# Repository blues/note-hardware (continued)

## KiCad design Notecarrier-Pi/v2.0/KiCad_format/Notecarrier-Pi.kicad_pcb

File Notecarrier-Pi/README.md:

# Notecarrier PI
Daughter board to integrate Notecard with Raspberry PI compatible hardware interface.
  - Schematics
  - Bills of material
  - PCB layouts and Gerber files
  - Dimensioned drawings
  - 3D models
  - KiCad design files ([v1.1/KiCad_format](v1.1/KiCad_format) and [v2.0/KiCad_format](v2.0/KiCad_format); v2.0 was authored in OrCAD/Allegro, for which no KiCad importer exists, so its port was built as a validated delta from the v1.1 port — see its [Porting-Notes](v2.0/KiCad_format/documentation/Porting-Notes.md))

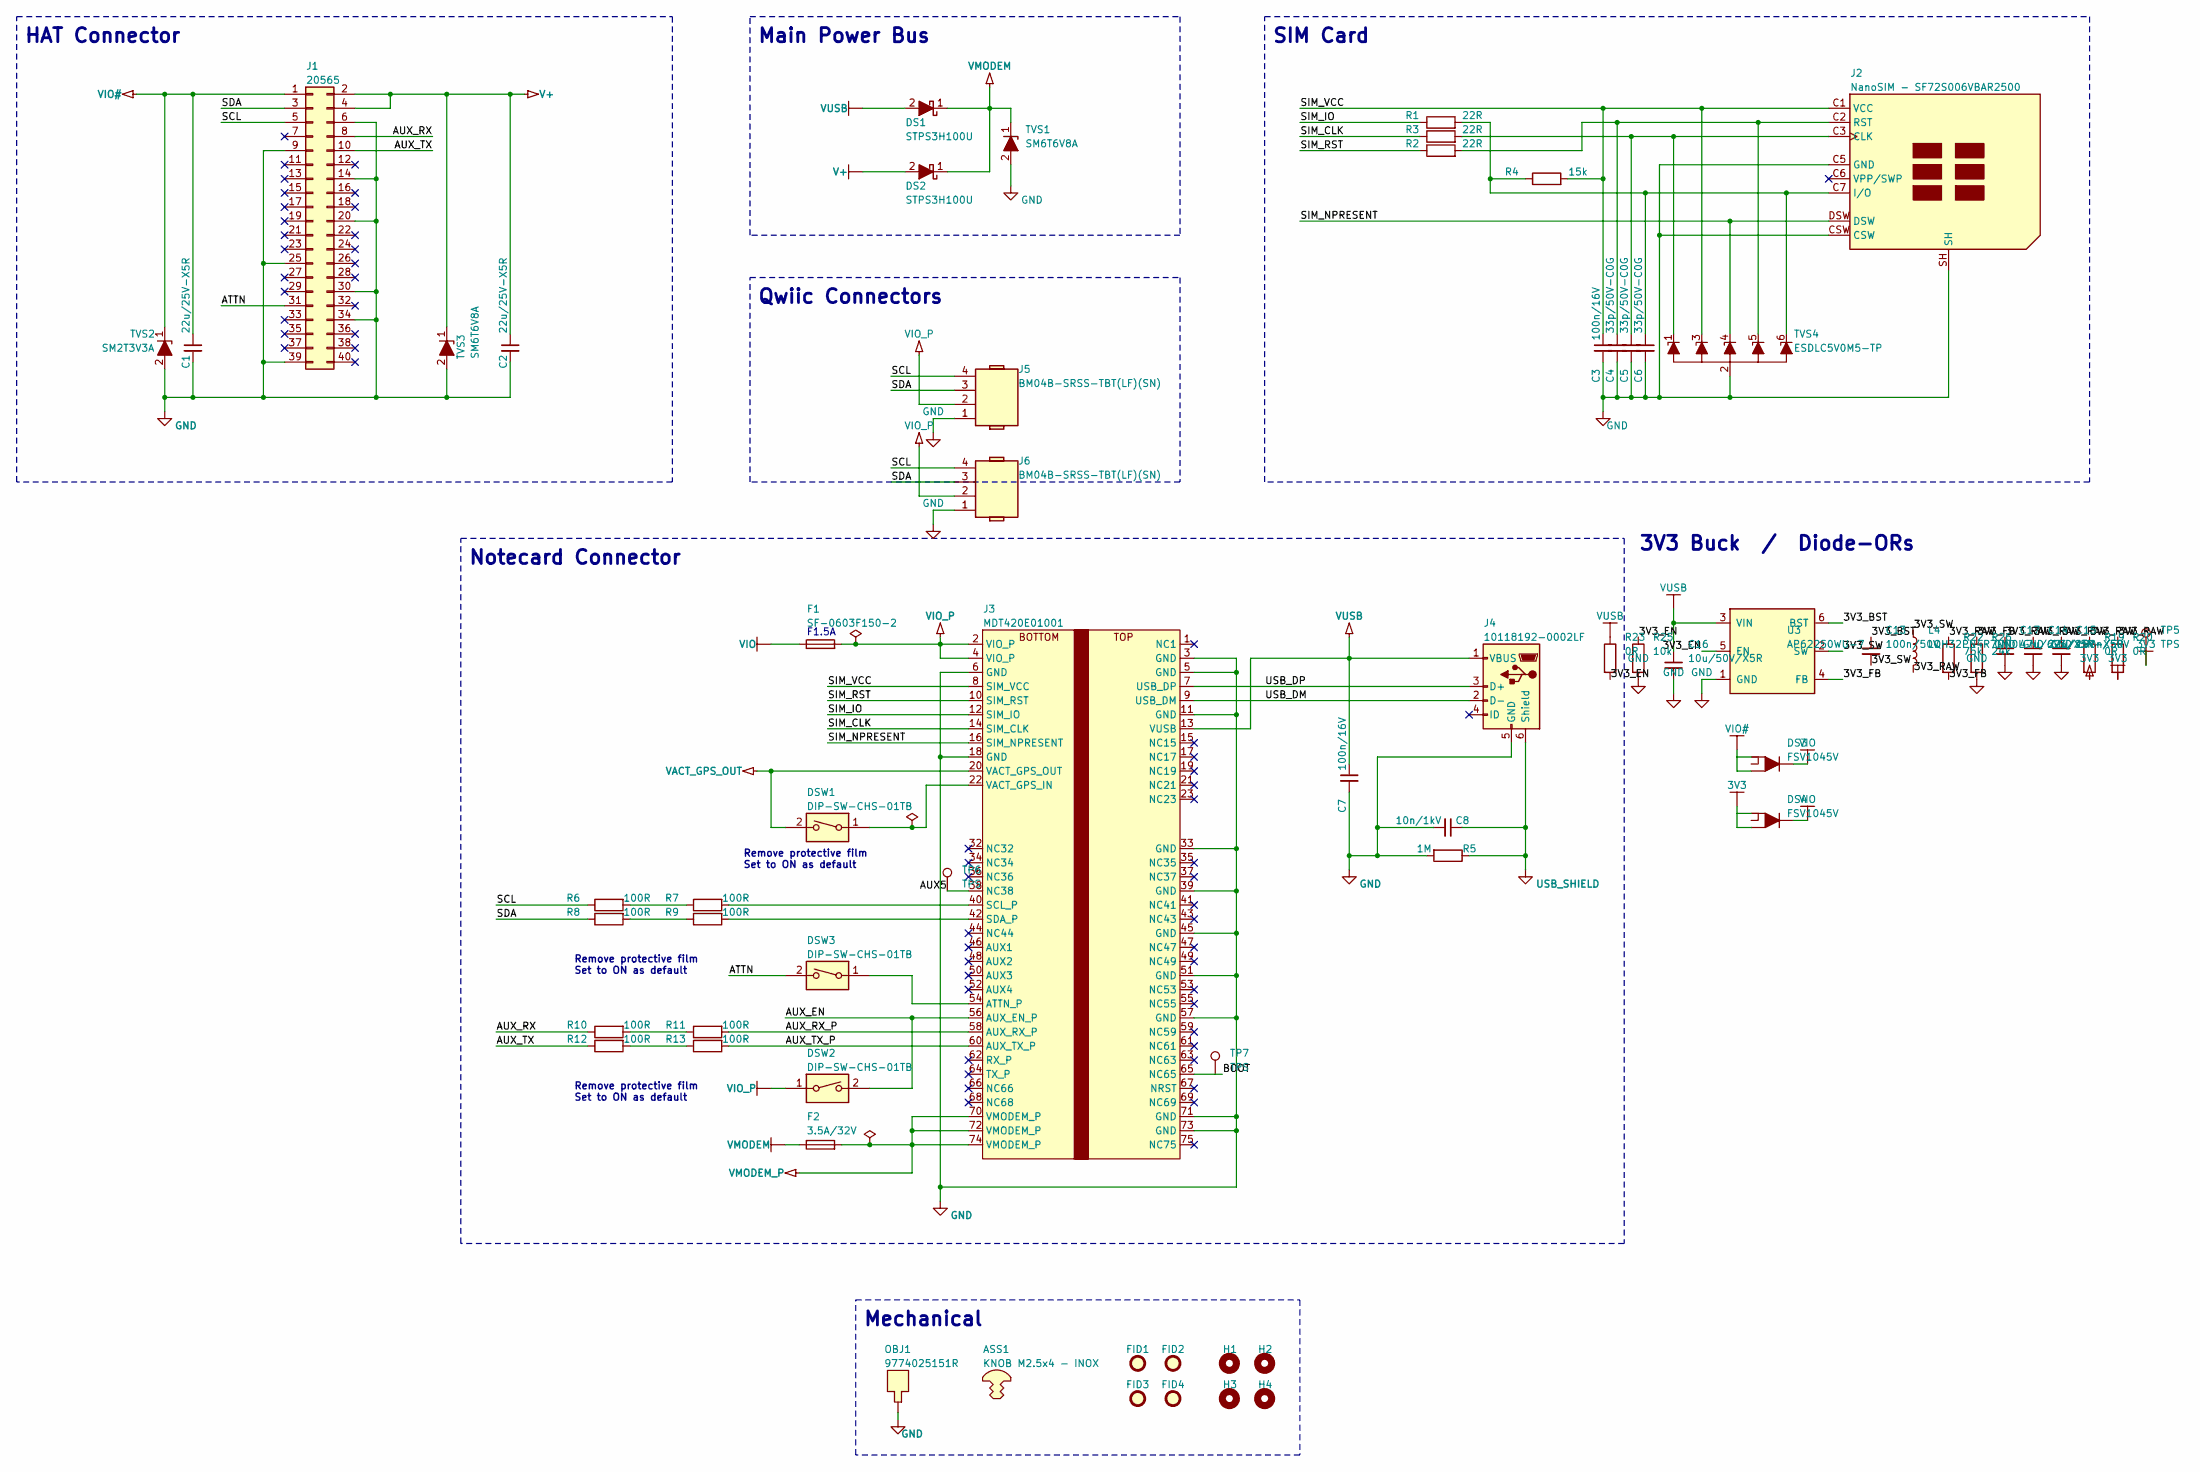
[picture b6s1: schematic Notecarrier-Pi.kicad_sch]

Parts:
ASS1: KNOB M2.5x4 - INOX; MPN 179-5691
C1, C2, C14: 22u/25V-X5R; CS-C-1206
C3, C7: 100n/16V; CS-C-0402
C4, C5, C6: 33p/50V-C0G; CS-C-0402
C8: 10n/1kV; CS-C-1206
C13, C15: 100n/50V; CS-C-0603
C16: 10u/50V/X5R; CS-C-1206
C17: 47u/6V3/X5R; CS-C-0603
DS1, DS2: STPS3H100U; SMB; MPN STPS3H100U
DS3, DS4: FSV1045V; TO277-3; MPN FSV1045V
DSW1, DSW2, DSW3: DIP-SW-CHS-01TB; DSS-CHS-01TB
F1: SF-0603F150-2; FS-0603; MPN SF-0603F150-2
F2: 3.5A/32V; FS-0603; MPN 0603SFV350F/32-2
FID1, FID2, FID3, FID4: TPS; FIDUCIAL
H1, H2, H3, H4: MountingHole; FORO-0270-U_smaller-clearance
J1: 20565; J-20x2-0254-FDT-SSQX03; MPN 20565
J2: NanoSIM - SF72S006VBAR2500; J-NANOSIM-SF72S006VBA_NO-FILL; MPN SF72S006VBAR2500
J3: MDT420E01001; J-75-0050-MOS-M2-E
J4: 10118192-0002LF; J-5-0065-FOS-USB10118192-NOF; MPN 10118192-0002LF
J5, J6: BM04B-SRSS-TBT(LF)(SN); J-4-0100-MDS-SH; MPN BM04B-SRSS-TBT(LF)(SN)
L4: LQH32PN4R7NN0L; LS-LQH32PN; MPN LQH32PN4R7NN0L
OBJ1: 9774025151R; DIST-WASMSIM0250
R1, R2, R3: 22R; RS-0603
R4: 15k; RS-0402
R5: 1M; RS-1206
R6, R7, R8, R9, R10, R11, R12, R13: 100R; RS-0402
R19, R20: 0R; RS-0603
R22: 75k; RS-0402
R23: 0R; RS-0402
R25: 10k; RS-0402
R26: 24k; RS-0402
TP5: TPS; TPS-0100
TP6, TP7: TPS; TPS-0150
TVS1, TVS3: SM6T6V8A; SMB
TVS2: SM2T3V3A; D-DO216AA_NO-SILK
TVS4: ESDLC5V0M5-TP; SOT666_NO-SILK
U3: AP62250WU-7; SOT23-6-DBV; MPN AP62250WU-7

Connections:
3V3: DS4.1 (A), DS4.2 (A), R19.2, R20.2, TP5.1
/3V3_BST: C13.1, U3.6 (BST)
/3V3_EN: R23.2, R25.1, U3.5 (EN)
/3V3_FB: R22.2, R26.1, U3.4 (FB)
/3V3_RAW: C14.1, C15.1, C17.1, L4.2, R19.1, R20.1, R22.1
/3V3_SW: C13.2, L4.1, U3.2 (SW)
/ATTN: DSW3.2, J1.31
/AUX5: J3.38 (NC38), TP6.1
/AUX_EN: DSW2.2, J3.56 (AUX_EN_P)
/AUX_RX: J1.8, R10.1
/AUX_RX_P: J3.58 (AUX_RX_P), R11.2
/AUX_TX: J1.10, R12.1
/AUX_TX_P: J3.60 (AUX_TX_P), R13.2
/BOOT: J3.65 (NC65), TP7.1
/SCL: J1.5, J5.4, J6.4, R6.1
/SDA: J1.3, J5.3, J6.3, R8.1
/SIM_CLK: J3.14 (SIM_CLK), R3.1
/SIM_IO: J3.12 (SIM_IO), R1.1
/SIM_NPRESENT: J2.DSW, J3.16 (SIM_NPRESENT), TVS4.4 (K3)
/SIM_RST: J3.10 (SIM_RST), R2.1
/SIM_VCC: C3.1, J2.C1 (VCC), J3.8 (SIM_VCC), R4.2, TVS4.3 (K2)
/USB_DM: J3.9 (USB_DM), J4.2 (D-)
/USB_DP: J3.7 (USB_DP), J4.3 (D+)
GND: C1.2, C2.2, C3.2, C4.2, C5.2, C6.2, C7.2, C8.2, C14.2, C15.2, C16.2, C17.2, J1.6, J1.9, J1.14, J1.20, J1.25, J1.30, J1.34, J1.39, J2.C5 (GND), J2.CSW, J2.SH, J3.3 (GND), J3.5 (GND), J3.6 (GND), J3.11 (GND), J3.18 (GND), J3.33 (GND), J3.39 (GND), J3.45 (GND), J3.51 (GND), J3.57 (GND), J3.71 (GND), J3.73 (GND), J4.5 (GND), J5.1, J6.1, OBJ1.1, R5.2, R25.2, R26.2, TVS1.2 (A2), TVS2.2 (A2), TVS3.2 (A2), TVS4.2 (A), U3.1 (GND)
unnamed: C5.1, J2.C3 (CLK), R3.2, TVS4.1 (K1)
unnamed: C6.1, J2.C7 (I/O), R1.2, R4.1, TVS4.6 (K5)
unnamed: C4.1, J2.C2 (RST), R2.2, TVS4.5 (K4)
unnamed: DSW3.1, J3.54 (ATTN_P)
unnamed: J3.40 (SCL_P), R7.2
unnamed: J3.42 (SDA_P), R9.2
unnamed: DSW1.1, J3.22 (VACT_GPS_IN)
unnamed: C8.1, J4.6 (Shield), R5.1
unnamed: R6.2, R7.1
unnamed: R8.2, R9.1
unnamed: R10.2, R11.1
unnamed: R12.2, R13.1
V+: C2.1, DS2.2 (A), J1.2, J1.4, TVS3.1 (A1)
VACT_GPS_OUT: DSW1.2, J3.20 (VACT_GPS_OUT)
VIO: DS3.3 (K), DS4.3 (K), F1.1
VIO#: C1.1, DS3.1 (A), DS3.2 (A), J1.1, TVS2.1 (A1)
VIO_P: DSW2.1, F1.2, J3.2 (VIO_P), J3.4 (VIO_P), J5.2, J6.2
VMODEM: DS1.1 (K), DS2.1 (K), F2.1, TVS1.1 (A1)
VMODEM_P: F2.2, J3.70 (VMODEM_P), J3.72 (VMODEM_P), J3.74 (VMODEM_P)
VUSB: C7.1, C16.1, DS1.2 (A), J3.13 (VUSB), J4.1 (VBUS), R23.1, U3.3 (VIN)

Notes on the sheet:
Main Power Bus
Remove protective film Set to ON as default
Mechanical
Qwiic Connectors
HAT Connector
F1.5A
Notecard Connector
SIM Card
3V3 Buck / Diode-ORs

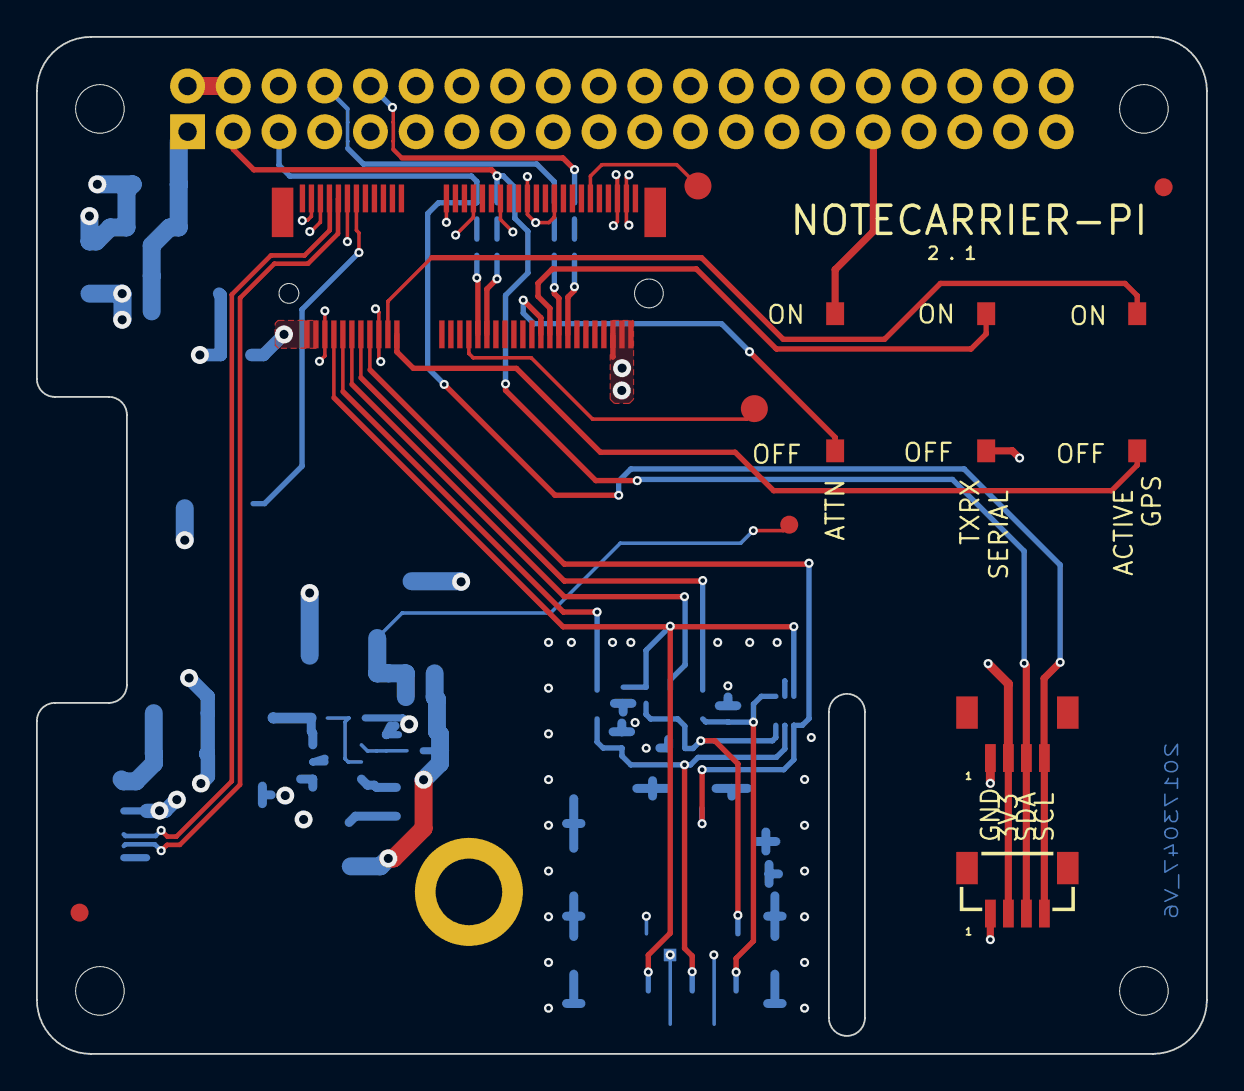
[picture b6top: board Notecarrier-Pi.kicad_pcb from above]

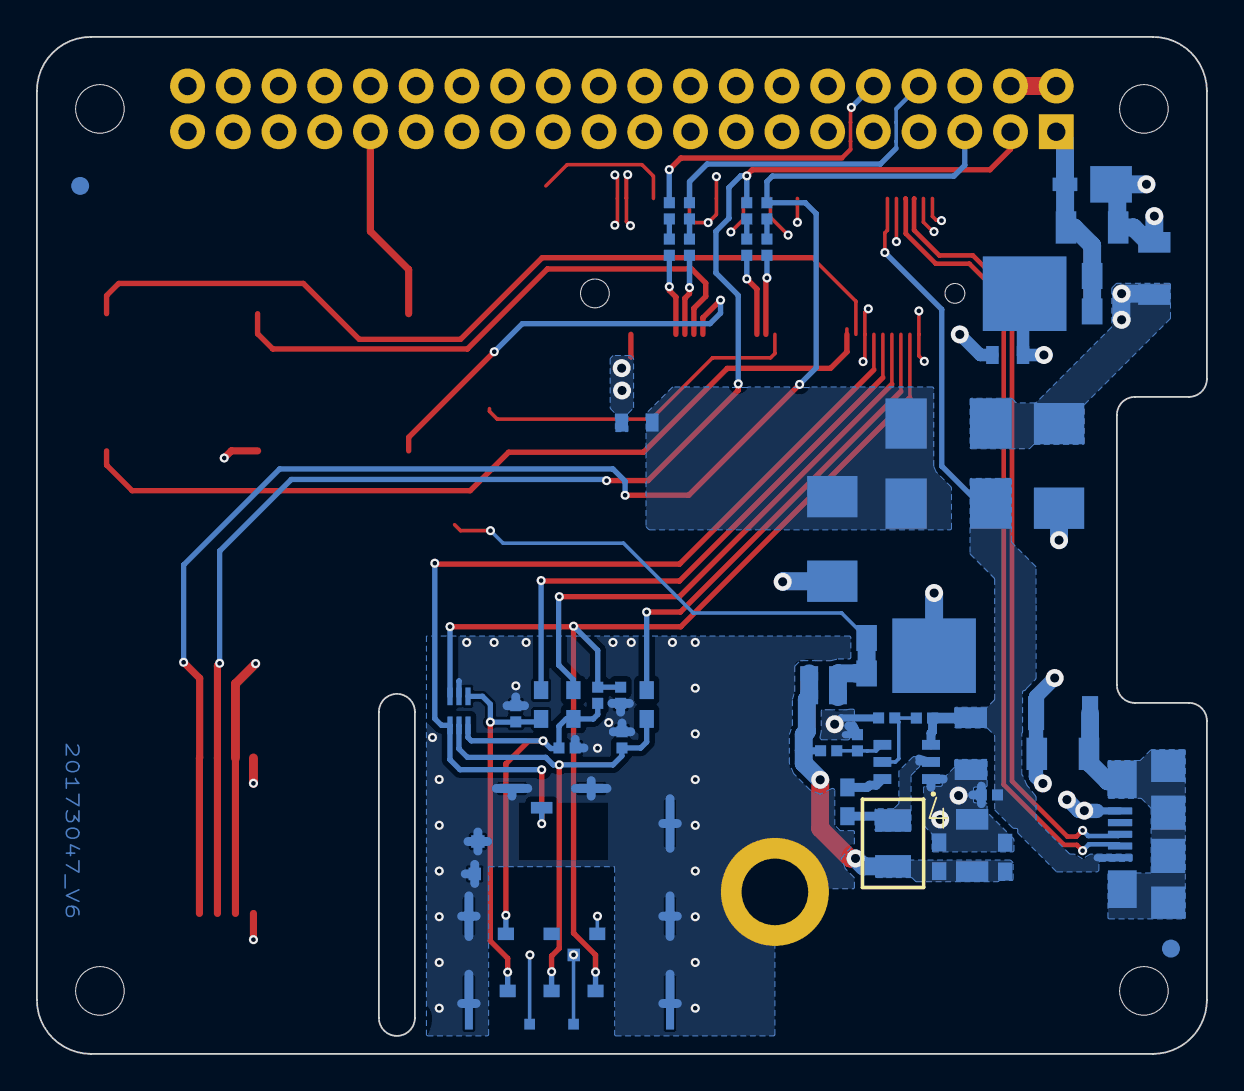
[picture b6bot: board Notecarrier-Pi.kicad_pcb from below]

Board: 4 copper layers, 65.0 x 56.5 mm, 65 parts (49 on the bottom side), 44 nets.

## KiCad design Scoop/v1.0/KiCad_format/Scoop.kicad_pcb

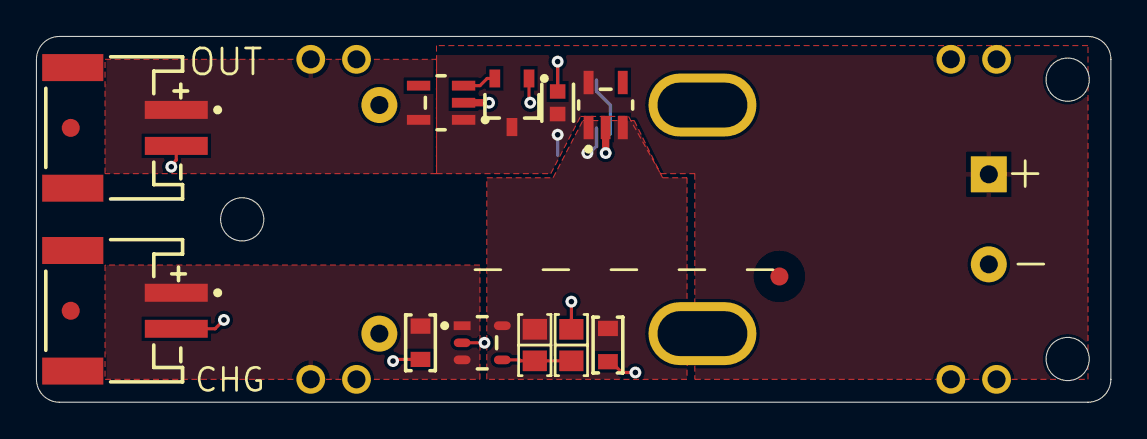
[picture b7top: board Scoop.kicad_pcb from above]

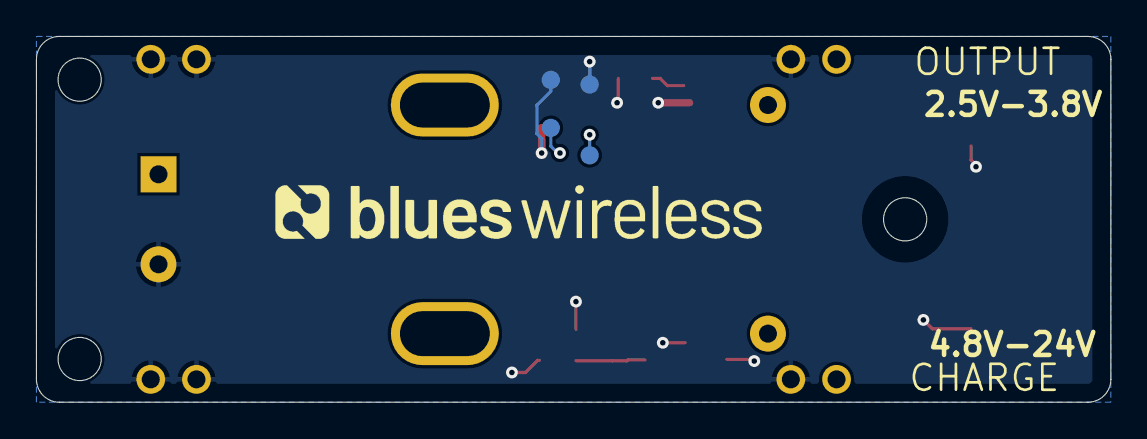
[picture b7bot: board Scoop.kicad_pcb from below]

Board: 2 copper layers, 59.7 x 20.3 mm, 31 parts (10 on the bottom side), 7 nets.

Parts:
+PROJECTID: Project ID; PROJECTID_MARK
C1, C4: CL21B105KBFNNNG; CAP FILM 0805
C2: VEL13353R8257G; VINA_VPC1335_RRA
C3: 0603YC105KAT2A; FP-0603-L_1_6_0_15-W_0_81-IPC_C
FD1, FD2, FD3: Global Fiducial; FID_1mm_3mm
HoldWire: Comment; VINA_VPC1335_HOLDWIRE
J1, J2: S2B-PH-SM4-TB(LF)(SN); BAT-AF-S2B-PH-SM4
J3, J4, J5, J6: Header 2-Pin, 0.100 inch (0.230 inch head); HEADER_AA_002_NO_SILK
LOGO: Comment; LOGO_BLUES_WIRELESS
MH1, MH2, MH5: M2; HOLE_2MM
MH3, MH4: 5mm slot; MHSLOT_2_5MM_5MM_WIDTH
R1: 178k; RES 0805_2012
R2: 82k; RES 0805_2012
U1: NCP718BSNADJT1G; FP-419AE-01-IPC_C
U2, U4: MAX40203AUK+T; FP-U5-2-MFG
U3: BD49K25G-TL; ROHM_SSOP3_N
Z1, Z2, Z3, Z4: Test Point; testp_40pad

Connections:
/3V8: C1.1, R1.2, U1.5 (OUT), U4.1 (VDD), U4.3 (EN), Z1.1
/3V8REGFB: R1.1, R2.2, U1.4 (ADJ)
/OUT_EN: U2.3 (EN), U3.2 (Vout)
/VBAT: C2.1, C3.1, U2.1 (VDD), U3.3 (Vdd), U4.5 (OUT), Z3.1
/VIN: C4.1, J1.1 (+), J3.1, U1.1 (IN), U1.3 (EN)
/VOUT: J2.1 (+), J4.1, U2.5 (OUT)
GND: C1.2, C2.2, C3.2, C4.2, J1.2 (-), J2.2 (-), J3.2, J4.2, J5.1, J5.2, J6.1, J6.2, R2.1, U1.2 (GND), U2.2 (GND), U3.1 (GND), U4.2 (GND), Z2.1, Z4.1

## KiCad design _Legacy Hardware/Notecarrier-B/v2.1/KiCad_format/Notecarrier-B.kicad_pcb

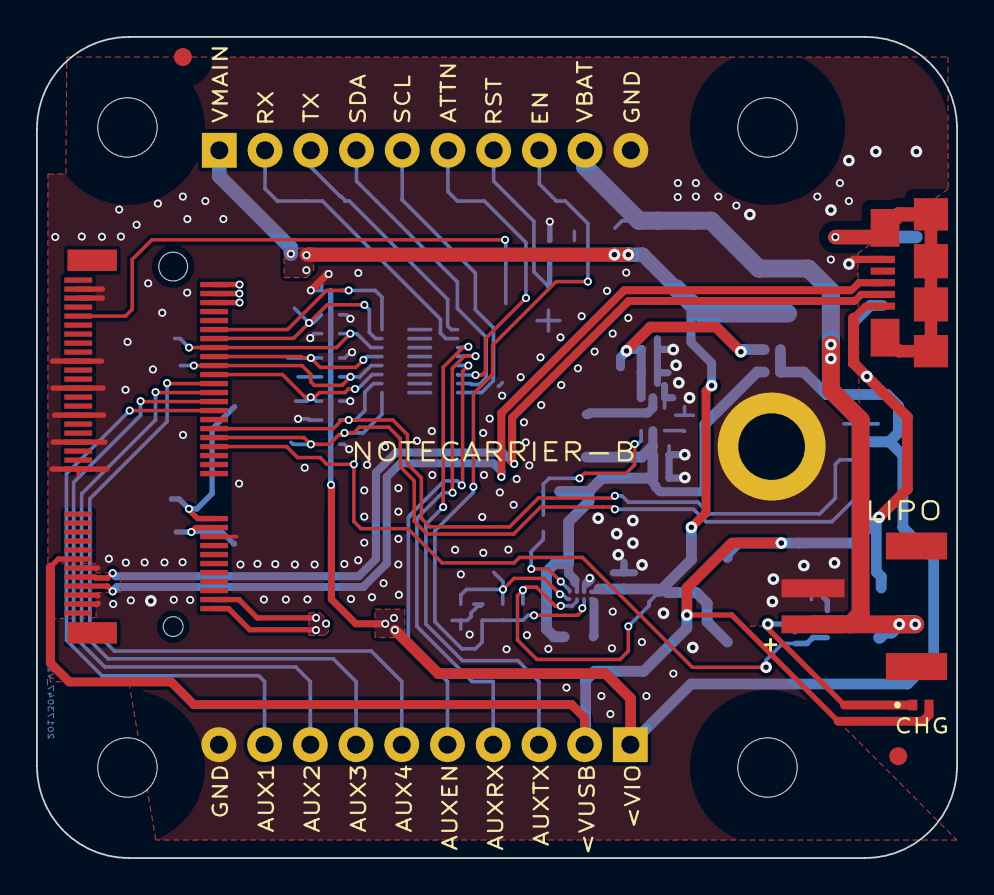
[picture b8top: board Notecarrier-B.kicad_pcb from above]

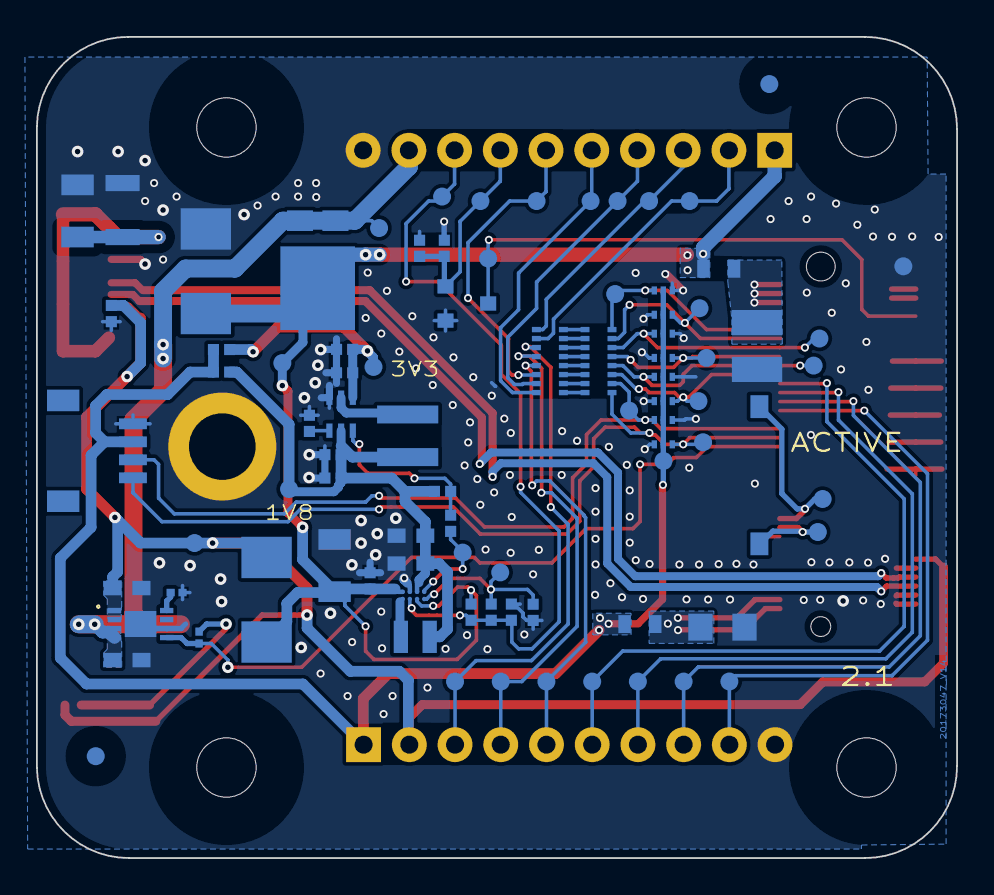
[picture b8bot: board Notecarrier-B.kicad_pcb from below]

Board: 2 copper layers, 51.1 x 45.6 mm, 96 parts (85 on the bottom side), 54 nets.

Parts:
C7, C10, C111, C115, C116: 100n/16V; CS-C-0402_NO-FILL
C8, C9: 10u/6.3V-X5R; CS-C-0402_NO-FILL
C13: 47u/16V-X5R; CS-C-1206
C14: 4.7u/6.3V-X5R; CS-C-0402_NO-FILL
C15, C16: 10u/10V-X5R; CS-C-0603
C112: 10n/1kV; CS-C-1206
C113: NU; CS-T-A
C114: NU; CS-T-B
C117, C118: 4.7u/10V/X5R; CS-C-0603
DS4, DS5, DS6, DS10: NU; SOT563
DS14: STPS3H100U; SMB
DS15: FSV1045V; TO277-3
DSW1: DIP-SW-CHS-01TB; DSS-CHS-01TB
F1: SF-0603F150-2; FS-0603
F2: 3.5A/32V; FS-0603
FID1, FID2, FID3, FID4: TPS; FIDUCIAL
H1, H2, H3, H4: MountingHole; FORO-0330-U
J19: MICROUSB-B; J-5-0065-FOS-MICROUSB10118192
J20: MDT420E01001; J-75-0050-MOS-M2-E
J21, J22: NU; J-10-0254-MDT
J23: S2B-PH-SM4-TB(LF)(SN); J-2-0200-MOS-S2B
J24: SM04B-SRSS-TBT; J-4-0100-MOS-SH
L2: 1285AS-H-2R2M=P2; LS-0806
L4: XFL4020-222MEC; LS-XFL4020
LD1: SML-P12WTT86R; LD-0402
OBJ1: 9774025151R; DIST-WASMSIM0250
Q2: AO3420; SOT23_NO-FILL
R5: 1k; RS-0201_NO-FILL
R6: 82k; RS-0402_NO-FILL
R7: 2.8k; RS-0201_NO-FILL
R10: 10M/5%; RS-0402_NO-FILL
R307: 1M; RS-1206
R318, R322, R325: 0R; RS-0402_NO-FILL
R319: 1k; RS-0402_NO-FILL
R323, R324, R326: NU; RS-0402_NO-FILL
RR1, RR2: 100R/5%; RR-8X-1506
TP1, TP2, TP3, TP4, TP5, TP6, TP7, TP8, TP10, TP11, TP12, TP13, TP14, TP15, TP17, TP18, TP20, TP21, TP22, TP23, TP24, TP25, TP26, TP28, TP29, TP30, TP31, TP32, TP33, TP34, TP38, TP39: TPS-SPEA
TVS1: SM6T6V8A; SMB
U3: MAX17225ELT; WDFN6-0200X0200
U4: TPS62748YFPT; XFBGA8
U5: MCP73831-2ACI/MC; VFDFN8-EXP
VMODEM: TPS-SPEA
VUSB: TPS-SPEA

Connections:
+1V8: C9.1, C10.1, C15.1, C16.1, L2.2, L4.2, R318.2, R326.2, TP12.1, U3.5 (IN), U4.C2 (VOS)
+3V3: C7.1, C8.1, R325.2, TP20.1, U3.1 (OUT)
/ATTN: J22.6, RR1.6 (R6.1), TP32.1
/ATTN_P: DS6.6 (K1A2), J20.54 (ATTN_P), RR2.11 (R6.2), TP18.1
/AUX1: J20.46 (AUX1), J21.9, TP1.1
/AUX2: J20.48 (AUX2), J21.8, TP2.1
/AUX3: J20.50 (AUX3), J21.7, TP3.1
/AUX4: J20.52 (AUX4), J21.6, TP7.1
/AUX5: J20.38 (NC38), R5.1, U5.5 (STAT)
/AUX_EN: J21.5, RR1.5 (R5.1), TP4.1
/AUX_EN_P: DS6.3 (K3A4), J20.56 (AUX_EN_P), RR2.12 (R5.2), TP21.1
/AUX_RX: J21.4, RR1.4 (R4.1), TP5.1
/AUX_RX_P: DS5.6 (K1A2), J20.58 (AUX_RX_P), RR2.13 (R4.2), TP22.1
/AUX_TX: J21.3, RR1.3 (R3.1), TP6.1
/AUX_TX_P: DS5.3 (K3A4), J20.60 (AUX_TX_P), RR2.14 (R3.2), TP23.1
/BOOST_EN: R324.2, TP10.1, U4.D2 (LOAD)
/EN: C116.1, J22.8, R10.1, R323.2, TP34.1, U4.B1 (EN)
/NRST: J20.67 (NRST), Q2.3 (D), TP26.1
/RST: C115.1, J22.7, Q2.1 (G), R319.2, TP33.1
/RX: J22.2, RR1.2 (R2.1), TP28.1
/RX_P: DS10.6 (K1A2), J20.62 (RX_P), RR2.15 (R2.2), TP24.1
/SCL: J22.5, RR1.8 (R8.1), TP31.1
/SCL_P: DS4.6 (K1A2), J20.40 (SCL_P), J24.4, RR2.9 (R8.2), TP15.1
/SDA: J22.4, RR1.7 (R7.1), TP30.1
/SDA_P: DS4.3 (K3A4), J20.42 (SDA_P), J24.3, RR2.10 (R7.2), TP17.1
/TX: J22.3, RR1.1 (R1.1), TP29.1
/TX_P: DS10.3 (K3A4), J20.64 (TX_P), RR2.16 (R1.2), TP25.1
/USB_DM: J19.2 (D-), J20.9 (USB_DM)
/USB_DP: J19.3 (D+), J20.7 (USB_DP)
GND: C7.2, C8.2, C9.2, C10.2, C13.2, C14.2, C15.2, C16.2, C111.2, C112.2, C113.2, C114.2, C115.2, C116.2, C117.2, C118.2, DS4.1 (A1), DS4.4 (A3), DS5.1 (A1), DS5.4 (A3), DS6.1 (A1), DS6.4 (A3), DS10.1 (A1), DS10.4 (A3), J19.5 (GND), J20.3 (GND), J20.5 (GND), J20.6 (GND), J20.11 (GND), J20.18 (GND), J20.33 (GND), J20.39 (GND), J20.45 (GND), J20.51 (GND), J20.57 (GND), J20.71 (GND), J20.73 (GND), J21.10, J22.10, J23.2, J24.1, OBJ1.1, Q2.2 (S), R6.1, R7.1, R307.2, R319.1, R322.1, TP38.1, TVS1.2 (A2), U3.3 (GND), U4.B2 (GND), U5.6 (V_{SS}), U5.9 (EP)
unnamed: C112.1, J19.6 (Shield), R307.1
unnamed: DSW1.1, J20.22 (VACT_GPS_IN)
unnamed: LD1.1 (K), R5.2
unnamed: RR1.16 (R1.2), RR2.1 (R1.1)
unnamed: RR1.15 (R2.2), RR2.2 (R2.1)
unnamed: RR1.14 (R3.2), RR2.3 (R3.1)
unnamed: RR1.13 (R4.2), RR2.4 (R4.1)
unnamed: RR1.12 (R5.2), RR2.5 (R5.1)
unnamed: RR1.11 (R6.2), RR2.6 (R6.1)
unnamed: RR1.10 (R7.2), RR2.7 (R7.1)
unnamed: RR1.9 (R8.2), RR2.8 (R8.1)
unnamed: R318.1, R324.1, U3.6 (EN)
unnamed: L4.1, U3.2 (LX)
unnamed: R6.2, U3.4 (SEL)
unnamed: R322.2, R323.1, TP8.1, U4.D1 (CTRL)
unnamed: L2.1, U4.A1 (SW)
unnamed: R7.2, U5.8 (PROG)
VACT_GPS_OUT: DSW1.2, J20.20 (VACT_GPS_OUT), TP11.1
VBAT: C117.1, DS15.1 (A1), DS15.2 (A2), J22.9, J23.1, TP39.1, U5.3 (V_{BAT}), U5.4 (V_{BAT})
VIO: DS4.2 (K2), DS4.5 (K4), DS5.2 (K2), DS5.5 (K4), DS6.2 (K2), DS6.5 (K4), DS10.2 (K2), DS10.5 (K4), F1.1, J21.1, J24.2, R325.1, R326.1, TP14.1
VIO_P: C113.1, F1.2, J20.2 (VIO_P), J20.4 (VIO_P)
VMODEM: C13.1, C14.1, DS14.1 (K), DS15.3 (C), F2.1, J22.1, R10.2, TVS1.1 (A1), U4.A2 (VIN), U4.C1 (VSEL), VMODEM.1
VMODEM_P: C114.1, F2.2, J20.70 (VMODEM_P), J20.72 (VMODEM_P), J20.74 (VMODEM_P)
VUSB: C111.1, C118.1, DS14.2 (A), J19.1 (VBUS), J20.13 (VUSB), J21.2, LD1.2 (A), U5.1 (V_{DD}), U5.2 (V_{DD}), VUSB.1

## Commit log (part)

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2020-03-24 first
2020-03-24 Adds code of conduct and contributing instructions
2020-03-24 Updates README
2020-10-05 Publish latest Notecarrier files
2020-10-06 Translate BOMs
2020-10-06 update README for note-hardware
2020-12-23 Remove Notecarrier-AF v6
2020-12-23 Add Notecarrier-AF v8
2020-12-23 add notecard dimension files
2020-12-25 Clean up BOMs and add supplier part numbers
2020-12-25 Remove Notecard stuff
2020-12-25 Notecard dimesioned drawings and models. Missing Notecarrier-AF files.
2020-12-25 Fix Notecarrier-AF
2020-12-25 Rename drawings
2020-12-25 Get rid of extra level of directories
2021-01-26 New version number scheme. Notecarrier-AF step file.
2021-03-30 Fixes broken "issues" link in CONTRIBUTING.md
2021-04-01 Notecarrier-AF schematic PDF
2021-04-01 feat: A-Series Solar App Note
2021-06-08 chore: migrate app notes to dev site
2021-06-09 fix: address code review feedback
2021-09-22 Swan
2021-09-28 add swan Eagle library file and Swan to readme
2021-10-06 Notecarrier-AL mountin holes.pdf
2021-10-06 Notecarrier-AF mounting holes.pdf
2022-01-07 NOTE-WIFI 3D model
2022-05-26 Notecarrier-A docs
2022-06-30 Airnote enclosure
2022-07-18 Mobile Tracker Hat
2022-07-19 Additional Mobile Tracker Hat directory
2022-08-09 Sparrow v1.1
2022-08-09 Fix filename extension
2022-10-03 Notecarrier-F v1.0
2022-10-26 Notecarrier-B 2.1 docs
2022-11-03 Add Swan v3.0 (move v1.7 to subfolder)
2022-11-03 Re-added Notecarrier B v1.6 Moved Notecarrier B versions into their own subfolders
2022-11-04 Swan v3.0
2022-11-07 Re-add v1.6. Move 2.1 to subfolder
2022-11-07 Add "old_versions" layer to Carr B folder to make it more obvious which is the most recent version
2022-12-19 added notecarrier-f dimensional drawing
2022-12-23 added 3d step file notecarrier-f
2022-12-31 Move depreciated items to subfolder. Add/Update readmes with item content info
2023-01-03 rename folder to _deprecated
2023-01-03 fix reference in README
2023-03-21 Start port of Notecarrier-B to KiCad format
    First draft of schematic and BOM port. Establish a file naming, folder
    hierarchy, gitignore and documentation strategy.
2023-03-22 Add footprints for Notecarrier-B
    See README changes for information on the motivation and approach.
2023-03-28 Port PCB and do validation for Notecarrier-B
2023-03-31 RevA: Add 3D models, validation script and output files
    Add a 3D model for each footprint, using method described in README.
    Re-ran validation to ensure output hadn't been compromised, so also added validation script and automation to README.
    Since validation script produces output files, officially marked them Rev A and added to repo.
2023-04-19 Add block diagram, separate porting notes, rename dirs
    A bunch of final touch-ups to the directory structure and some
    organisations of the documentation.
2023-04-19 Start Notecarrier-F port. Add block diagram.
2023-04-20 Move all Notecarrier-B parts into blues-kicad-lib
    - all symbols, footprints and 3d-models which lived in the Notecarrier-B project consolidated into the blues-kicad-lib library.
    - the BLUES_KICAD_LIB_DIR environment variable created and all links updated.
    - PortingNotes.md updated with the rationale and method
    - README.md updated with a reference to the library in accordance with the rationale in PortingNotes.
2023-04-20 Establish Notecarrier-F KiCad project files and paths
2023-04-25 Port Notecarrier-F schematic and BOM.
2023-04-26 Ported footprint assignments, board outline, copper layers and dimensional drawings for Notecarrier-F.
    Footprints currently held in a “blues-kicad-lib-pending” library, prior to merging with “blues-kicad-lib” and deleting unused items.
2023-04-28 Finish first pass PCB port.
    Still need to go back and finalise top-level schematic sheet.
    Next step is validation where there’s bound to be lots of copper rules to tweak.
2023-05-01 Final touches to first pass PCB and porting notes.
2023-05-02 Apply first pass validation of Notecarrier-F port
    Huge push to identify, solve, document and revalidate all the details revealed by the first run of the validation process. Validation is now acceptable and preparation can be made to release Rev A.
2023-05-03 Release Rev A of Notecarrier-F KiCad port.
2023-05-11 Create new project template for Notecarrier-A port, based on Notecarrier-B port.
2023-05-12 Add Rev A of Notecarrier-A block diagram port.
2023-05-12 Add first pass of port of Notecarrier-A Power sheet.
2023-05-12 Back fill symbol for SM04B-SRSS-TB / BM04B-SRSS-TBT.
    Symbol created in the process of porting Notecarrier-A. Creating the symbol wasn’t justified when porting -B and -F, now it exists it’s best to be consistent even though these are SM04B-SRSS-TB (side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
2023-05-12 Add first pass of port of Notecarrier-A Connector sheet.
    First pass port of schematics now complete. Next step: BOM.
2023-05-15 Fix URL link to PortingNotes.md
2023-05-16 Correct BQ24210DQCT BAT pin to Power Input.
    Realised it was incorrectly specified as a Power Output while porting Notecarrier-A. It’s the battery itself which is the source of power, so even though this pin provides charging current, it must b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
2023-05-16 Update visual aspects of SOT666 and J-NANOSIM footprints.
    Update to footprints modified during Notecarrier-A port, which moves some non-copper elements between layers to better suit both projects. See PortingNotes for details.
2023-05-17 Backport name change from `RS-0402` to `RS-0402_NO-FILL`.
    Name changed in Notecarrier-A port. See those PortingNotes for details. Also performed long overdue “update PCB from schematic” - remember that the test points are not in the schematic, so must be pr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
2023-05-18 Correct netclass name filter and track porting script.
    Minors improvements to Notecarrier-B found during port of Notecarrier-A:
    - The name of the USB shield had changed, so I updated the corresponding netclass filter.
    - And in the script used to port the tracks from OrCAD, I increased the maximum size from 1mm to 2mm to suit the bigger ones found in Notecarrier-A.
2023-05-18 Establish port of Notecarrier-B PCB.
    Ported: components, board outline, fabrication layers, silkscreens and front copper.
    To go: inner and back copper layers, drills, sheet metadata.
2023-05-19 First pass port of Notecarrier-B PCB.
    See PortingNotes for details. To go: 3D models and validation.
2023-05-22 Set all testpoints to “Not in schematic”.
    After backporting improvements from the Notecarrier-A port, I realised that updating the PCB from the schematic can delete all the testpoints, because they have been added at the PCB level. In Noteca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
2023-05-22 Clarify validation procedure to suit Notecarrier-A as well.
2023-05-23 Backport SOT23 footprint name change from Notecarrier-A.
2023-05-23 Release RevA of Notecarrier-A port.
    Validation complete. Results in the validation directory, documented in PortingNotes.md.
2023-05-24 Complete README, add references.
2023-05-24 Establish Notecarrier-Pi port project.
    Mostly empty but based on Notecarrier-A project.
2023-05-25 First pass port of Notecarrier-Pi schematic.
2023-05-26 Port fab, silk and copper layers for Notecarrier-Pi.
2023-05-26 Create rules and clearances to suit Notecarrier-Pi port.
    Also, fix VIO_P power symbol which had VIO net name.
2023-05-29 Complete validation of Notecarrier-Pi port.
2023-05-29 Back port J-5-0065-FOS-USB10118192-NOF footprint from Notecarrier-Pi.
2023-05-29 Release Rev A of Notecarrier-Pi port.
2023-05-30 Re-gen Gerbers in 7.0.5 to fix mask expansion bug.
    - Bug fixed: https://gitlab.com/kicad/code/kicad/-/issues/14693
    - See PortingNotes.md diff for details.
    - Also tweaked location of text on B.Cu and Silkscreen layers to compensate for improvements in text positioning: https://gitlab.com/kicad/code/kicad/-/issues/14755
    - Rather than restore original location, worked to make it even truer to original. All very minor, but better.
2023-05-31 Re-gen Notecarrier-Pi Gerbers in KiCad 7.0.5 to fix mask expansion bug.
    - Bug fixed: https://gitlab.com/kicad/code/kicad/-/issues/14693
    - See Notecarrier-A PortingNotes.md history for details.
    - Also tweaked location of some text on B.Cu and F.Silkscreen layers to compensate for improvements in text positioning: https://gitlab.com/kicad/code/kicad/-/issues/14755
    - Rather than restore previous location, worked to make it even truer to original where the previous location wasn’t an improvement. All very minor, but better.
2023-06-23 Add readme for Notecarrier-F KiCad port
    Overlooked when port was done. Should have been there from the start.
2023-06-26 Start rev B of Notecarrier-F port
    Incorporates changes from Altium design files rev 10 (PCB version 1.2).
    Block diagram and schematic first pass complete.
2023-07-03 Complete first pass PCB rev B.
    See README for details. Ready to start Validation.
2023-07-18 Update footprints after adding 3D models and tweaking weird-no-fill-via.
2023-07-18 Apply cosmetic tweaks from Validation activity.
    - Remove 4 way junction.
    - Remove off-grid connections.
    - Correct visible component values
    - Add missing design notes.
2023-07-18 Apply minor corrections from BOM validation.
2023-07-18 Complete validation.
    A few minor touch-ups to fills, polygons and DRC exclusions.
    Most significantly, re-assigned “GND” net to most (all?) of the weird-no-fill-via footprints, which got unassigned in a previous update-from-libraries. Also locked them all to reduce likely of losing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
2023-07-18 Release Rev B of Notecarrier-F KiCad port.
2023-07-19 Add note on decision to not port panel.
2023-07-21 Fix link to PortingNotes.
2023-10-17 feat: add step file for scoop
2023-10-25 adding 3D models of all new Notecard models
2023-11-13 Scoop
2023-11-27 added CARR-F v1.3
2024-01-04 adding CARR-PI v2 files
2024-01-04 3d model file directory
2024-01-04 fix link
2024-03-18 reorganizing directories and adding CARR-R files
2024-03-18 carr-b 3.1 files
2024-06-06 xs files
2024-06-10 fix: moving kicad files into the appropriate version directories for B and F
2024-07-18 feat: Notecarrier XS v1.2
2024-09-13 notecarrier x, xm, xp schematics and associated files
2024-10-10 rename old lora model, add v2.1 model
2024-11-29 add dimension drawings for v3.2 Notecards
2024-12-02 add v3.2 step files
2024-12-17 add cygnet
2025-01-23 add mojo
2025-02-07 fix: update CARR-F 1.3 schematics and associated files
2025-02-12 fix: Fixing XS diagram. Notecard <-> Starnote is UART, not I2C.
2025-04-30 feat: README cleanup and moving Sparrow to _deprecated
2025-04-30 tweaks from review
2025-04-30 feat: adds BIM2005 enclosure bracket
2025-05-22 feat: adding Karl's folding enclosures for Notecarrier A/F
2025-05-23 add Pi carrier V2 Schematic
2025-07-09 add starnote stp files
2025-11-19 note-hardware organization
    move CARR-B to deprecated, rename two other dirs
2026-05-13 CX 1.7
2026-05-13 move R to deprecated
2026-05-13 rename "deprecated" to "legacy"
2026-05-13 add Notecarrier A v2.3 files
2026-05-22 add step file for opta
2026-05-28 add notecarrier xi
2026-05-28 fix version number
2026-06-15 Adding Midband (LTE Cat-1bis) 3D model files
2026-06-25 draft of new rag source
2026-06-25 switch from md to html and move tools directory
2026-06-25 prevent indexing
2026-06-25 node 20 --> 24
